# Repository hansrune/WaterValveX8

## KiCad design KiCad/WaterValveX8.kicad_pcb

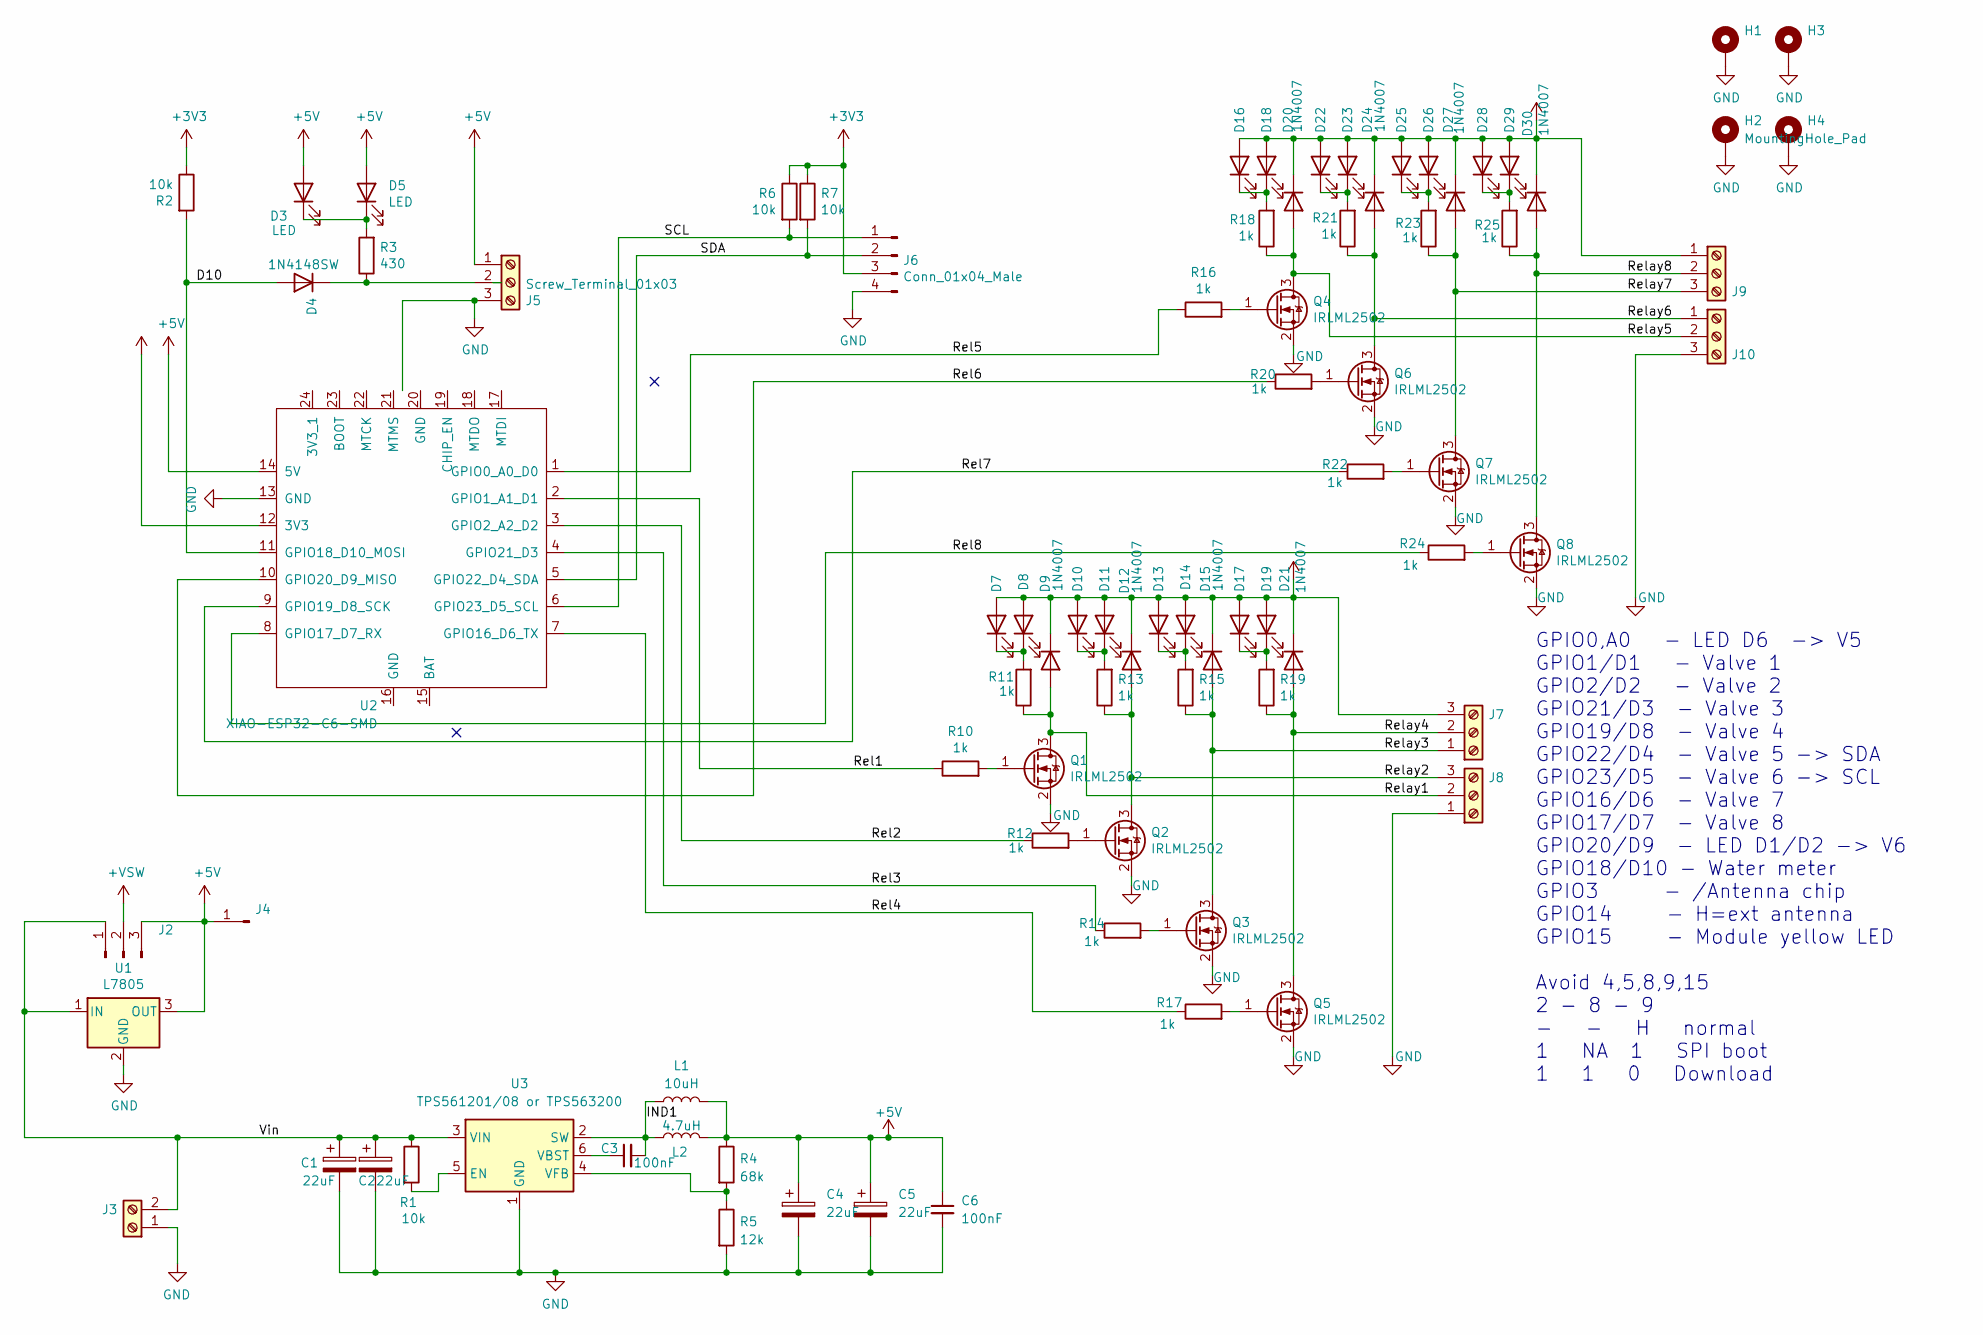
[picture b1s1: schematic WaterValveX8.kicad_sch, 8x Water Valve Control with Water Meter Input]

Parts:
C1, C2: 22uF; C_1206_3216Metric_Pad1.33x1.80mm_HandSolder
C3, C6: 100nF; C_0805_2012Metric_Pad1.18x1.45mm_HandSolder
C4, C5: 22uF; C_1206_3216Metric_Pad1.33x1.80mm_HandSolder; JLCPCB Part# C45783
D3, D8, D11, D14, D18, D19, D23, D26, D29: LED; LED_0805_2012Metric_Pad1.15x1.40mm_HandSolder
D4: 1N4148SW; D_SOD-323_HandSoldering
D5, D7, D10, D13, D16, D17, D22, D25, D28: LED; LED_D3.0mm
D9, D12, D15, D20, D21, D24, D27, D30: 1N4007; D_SOD-323_HandSoldering
H1, H2, H3, H4: MountingHole_Pad; MountingHole_3.2mm_M3_ISO14580_Pad
J2: Conn_01x03_Male; PinHeader_1x03_P2.54mm_Vertical
J3: Screw_Terminal_01x02; TerminalBlock_Phoenix_PT-1,5-2-3.5-H_1x02_P3.50mm_Horizontal
J4: Conn_01x01_Male; PinHeader_1x01_P2.54mm_Vertical
J5, J7, J8, J9, J10: Screw_Terminal_01x03; TerminalBlock_Phoenix_PT-1,5-3-3.5-H_1x03_P3.50mm_Horizontal
J6: Conn_01x04_Male; PinHeader_1x04_P2.54mm_Vertical
L1: 10uH; L_Bourns-SRU8028_8.0x8.0mm; JLCPCB Part# C2929438
L2: 4.7uH; L_2010_5025Metric_Pad1.52x2.65mm_HandSolder; JLCPCB Part# C2929438
Q1, Q2, Q3, Q4, Q5, Q6, Q7, Q8: IRLML2502; SOT-23_Handsoldering
R1: 10k; R_0805_2012Metric_Pad1.20x1.40mm_HandSolder; JLCPCB Part# C4328
R2, R6, R7: 10k; R_0805_2012Metric_Pad1.20x1.40mm_HandSolder
R3: 430; R_0805_2012Metric_Pad1.20x1.40mm_HandSolder
R4: 68k; R_0805_2012Metric_Pad1.20x1.40mm_HandSolder; JLCPCB Part# C17850
R5: 12k; R_0805_2012Metric_Pad1.20x1.40mm_HandSolder; JLCPCB Part# C4328
R10, R11, R12, R13, R14, R15, R16, R17, R18, R19, R20, R21, R22, R23, R24, R25: 1k; R_0805_2012Metric_Pad1.20x1.40mm_HandSolder
U1: L7805; TO-220-3_Vertical
U2: XIAO-ESP32-C6-SMD
U3: TPS561201/08 or TPS563200; SOT-23-6

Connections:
+3V3: J6.3, R2.1, R6.1, R7.1, U2.12 (3V3)
+5V: C4.1, C5.1, C6.1, D3.2 (A), D5.2 (A), J2.3, J4.1, J5.1, L1.2, L2.2, R4.1, U1.3 (OUT), U2.14 (5V)
+VSW: D7.2 (A), D8.2 (A), D9.1 (K), D10.2 (A), D11.2 (A), D12.1 (K), D13.2 (A), D14.2 (A), D15.1 (K), D16.2 (A), D17.2 (A), D18.2 (A), D19.2 (A), D20.1 (K), D21.1 (K), D22.2 (A), D23.2 (A), D24.1 (K), D25.2 (A), D26.2 (A), D27.1 (K), D28.2 (A), D29.2 (A), D30.1 (K), J2.2, J7.3, J9.1
/D10: D4.2 (A), R2.2, U2.11 (GPIO18_D10_MOSI)
/IND1: C3.2, L1.1, L2.1, U3.2 (SW)
/Rel1: R10.1, U2.2 (GPIO1_A1_D1)
/Rel2: R12.1, U2.3 (GPIO2_A2_D2)
/Rel3: R14.1, U2.4 (GPIO21_D3)
/Rel4: R17.1, U2.7 (GPIO16_D6_TX)
/Rel5: R16.1, U2.1 (GPIO0_A0_D0)
/Rel6: R20.1, U2.10 (GPIO20_D9_MISO)
/Rel7: R22.1, U2.9 (GPIO19_D8_SCK)
/Rel8: R24.1, U2.8 (GPIO17_D7_RX)
/Relay1: D9.2 (A), J8.2, Q1.3 (D), R11.1
/Relay2: D12.2 (A), J8.3, Q2.3 (D), R13.1
/Relay3: D15.2 (A), J7.1, Q3.3 (D), R15.1
/Relay4: D21.2 (A), J7.2, Q5.3 (D), R19.1
/Relay5: D20.2 (A), J10.2, Q4.3 (D), R18.1
/Relay6: D24.2 (A), J10.1, Q6.3 (D), R21.1
/Relay7: D27.2 (A), J9.3, Q7.3 (D), R23.1
/Relay8: D30.2 (A), J9.2, Q8.3 (D), R25.1
/SCL: J6.1, R6.2, U2.6 (GPIO23_D5_SCL)
/SDA: J6.2, R7.2, U2.5 (GPIO22_D4_SDA)
/Vin: C1.1, C2.1, J2.1, J3.2, R1.1, U1.1 (IN), U3.3 (VIN)
GND: C1.2, C2.2, C4.2, C5.2, C6.2, H1.1, H2.1, H3.1, H4.1, J3.1, J5.3, J6.4, J8.1, J10.3, Q1.2 (S), Q2.2 (S), Q3.2 (S), Q4.2 (S), Q5.2 (S), Q6.2 (S), Q7.2 (S), Q8.2 (S), R5.2, U1.2 (GND), U2.13 (GND), U3.1 (GND)
unnamed: D3.1 (K), D5.1 (K), R3.2
unnamed: D4.1 (K), J5.2, R3.1
unnamed: D7.1 (K), D8.1 (K), R11.2
unnamed: D10.1 (K), D11.1 (K), R13.2
unnamed: D13.1 (K), D14.1 (K), R15.2
unnamed: D16.1 (K), D18.1 (K), R18.2
unnamed: D17.1 (K), D19.1 (K), R19.2
unnamed: D22.1 (K), D23.1 (K), R21.2
unnamed: D25.1 (K), D26.1 (K), R23.2
unnamed: D28.1 (K), D29.1 (K), R25.2
unnamed: Q1.1 (G), R10.2
unnamed: Q2.1 (G), R12.2
unnamed: Q3.1 (G), R14.2
unnamed: Q4.1 (G), R16.2
unnamed: Q5.1 (G), R17.2
unnamed: Q6.1 (G), R20.2
unnamed: Q7.1 (G), R22.2
unnamed: Q8.1 (G), R24.2
unnamed: R1.2, U3.5 (EN)
unnamed: C3.1, U3.6 (VBST)
unnamed: R4.2, R5.1, U3.4 (VFB)

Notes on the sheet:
GPIO0,A0 - LED D6 -> V5 GPIO1/D1 - Valve 1 GPIO2/D2 - Valve 2 GPIO21/D3 - Valve 3 GPIO19/D8 - Valve 4 GPIO22/D4 - Valve 5 -> SDA GPIO23/D5 - Valve 6 -> SCL GPIO16/D6 - Valve 7 GPIO17/D7 - Valve 8 GPIO20/D9 - LED D1/D2 -> V6 GPIO18/D10 - Water meter GPIO3 - /Antenna chip GPIO14 - H=ext antenna GPIO1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

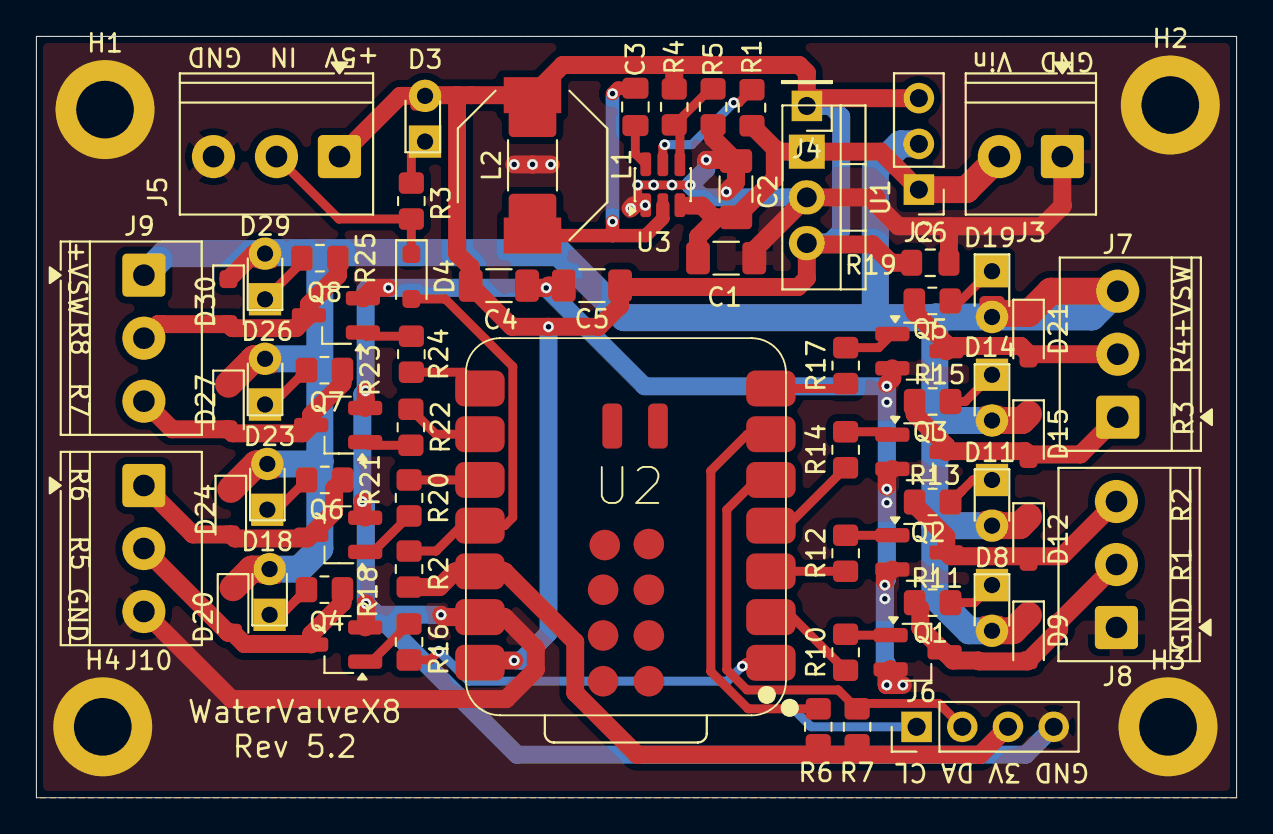
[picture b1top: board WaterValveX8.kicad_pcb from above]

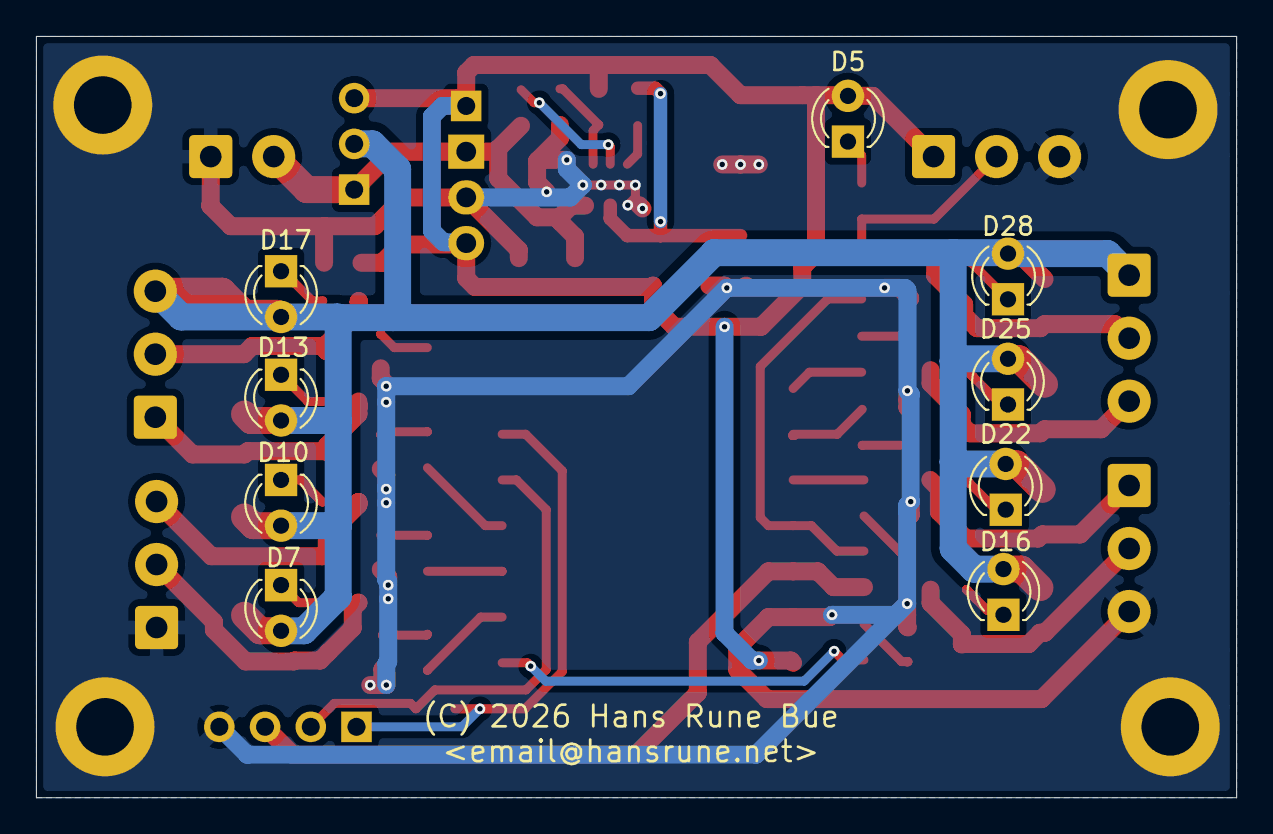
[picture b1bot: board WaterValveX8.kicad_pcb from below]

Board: 2 copper layers, 66.7 x 42.3 mm, 82 parts (9 on the bottom side), 46 nets.

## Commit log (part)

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2025-10-15 X4 -> X8
2025-10-15 First X8 layout
2025-10-20 Diode footprint changes
2025-10-27 Changed to combined C3/C6 and step-down PSU
2025-10-28 Add print files for 8.0
2025-10-28 Add gerber to .gitignore
2025-10-28 Missing files/updates for v4.0
2025-10-28 Removed unintentional commit
2025-10-28 Title is 8x - not 4
2025-11-18 Now a esp32c6 design only. To few usable ports on c3
2026-01-04 Moved power in to top right

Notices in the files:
KiCad/WaterValveX8.kicad_pcb:
(C) 2026 Hans Rune Bue
KiCad/WaterValveX8.kicad_sch:
Copyright - Hans Rune Bue
Hardware is licensed under CERN-OHL-W-2.0
Project documents are licensed under CC-BY-SA 2.0
